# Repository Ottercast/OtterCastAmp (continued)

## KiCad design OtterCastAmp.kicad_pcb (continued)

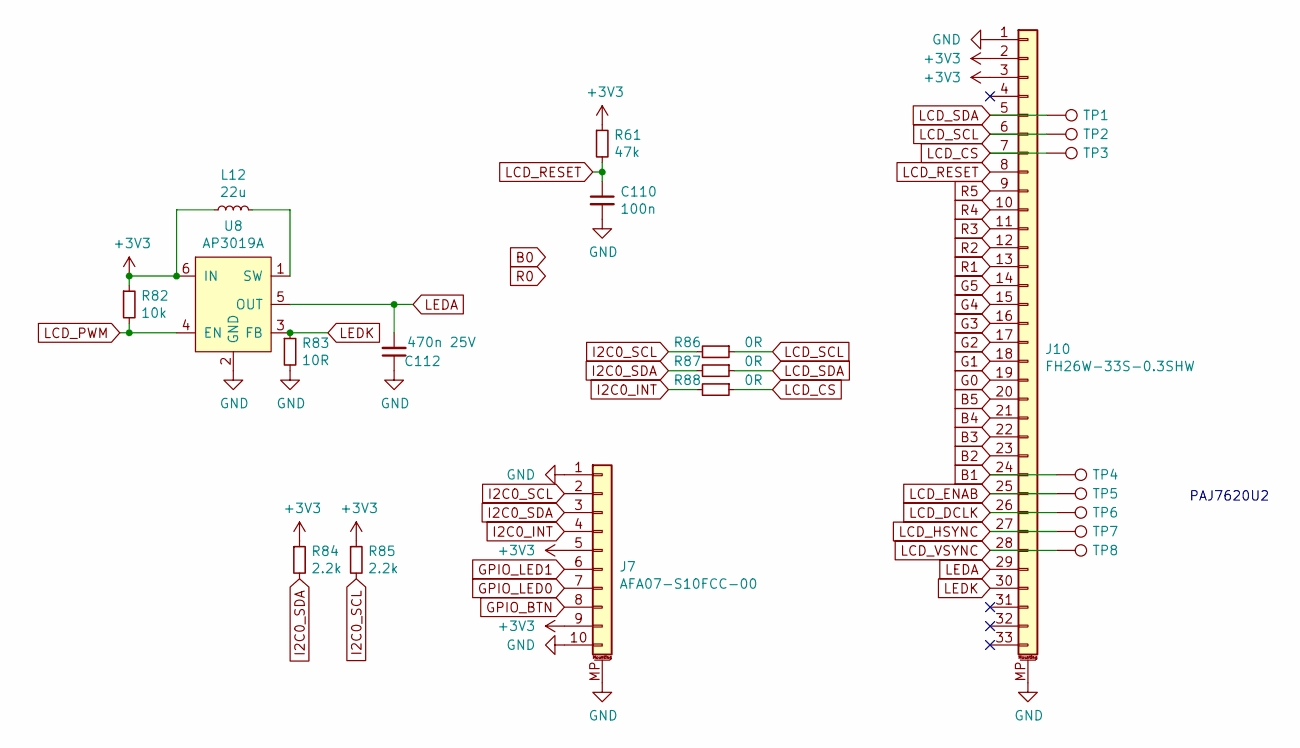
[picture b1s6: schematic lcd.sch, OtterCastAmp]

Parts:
C110: 100n; C_0402
C112: 470n 25V; C_0603
J7: AFA07-S10FCC-00; TE_1-84952-0_1x10-1MP_P1.0mm_Horizontal
J10: FH26W-33S-0.3SHW; Molex_502250-3391_2Rows-33Pins-1MP_P0.60mm_Horizontal
L12: 22u; Inductor_4040
R61: 47k; R_0402
R82: 10k; R_0402
R83: 10R; R_0402
R84, R85: 2.2k; R_0402
R86, R87, R88: 0R; R_0402
TP1, TP2, TP3, TP4, TP5, TP6, TP7, TP8: TestPoint; TestPoint_Pad_1.0x1.0mm
U8: AP3019A; SOT-23-6

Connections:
B1: J10.24, TP4.1; also elsewhere on the board
B2: J10.23; also elsewhere on the board
B3: J10.22; also elsewhere on the board
B4: J10.21; also elsewhere on the board
B5: J10.20; also elsewhere on the board
G0: J10.19; also elsewhere on the board
G1: J10.18; also elsewhere on the board
G2: J10.17; also elsewhere on the board
G3: J10.16; also elsewhere on the board
G4: J10.15; also elsewhere on the board
G5: J10.14; also elsewhere on the board
GND: C110.2, C112.1, J7.1, J7.10, J7.MP (MountPin), J10.1, J10.MP (MountPin), R83.2, U8.2 (GND); also elsewhere on the board
GPIO_BTN: J7.8; also elsewhere on the board
GPIO_LED0: J7.7; also elsewhere on the board
GPIO_LED1: J7.6; also elsewhere on the board
I2C0_INT: J7.4, R88.2; also elsewhere on the board
I2C0_SCL: J7.2, R85.2, R86.2; also elsewhere on the board
I2C0_SDA: J7.3, R84.2, R87.2; also elsewhere on the board
LCD_CS: J10.7, R88.1, TP3.1; also elsewhere on the board
LCD_DCLK: J10.26, TP6.1; also elsewhere on the board
LCD_ENAB: J10.25, TP5.1; also elsewhere on the board
LCD_HSYNC: J10.27, TP7.1; also elsewhere on the board
LCD_PWM: R82.2, U8.4 (EN); also elsewhere on the board
LCD_RESET: C110.1, J10.8, R61.2
LCD_SCL: J10.6, R86.1, TP2.1; also elsewhere on the board
LCD_SDA: J10.5, R87.1, TP1.1; also elsewhere on the board
LCD_VSYNC: J10.28, TP8.1; also elsewhere on the board
LEDA: C112.2, J10.29, U8.5 (OUT)
LEDK: J10.30, R83.1, U8.3 (FB)
unnamed: L12.2, U8.1 (SW)
R1: J10.13; also elsewhere on the board
R2: J10.12; also elsewhere on the board
R3: J10.11; also elsewhere on the board
R4: J10.10; also elsewhere on the board
R5: J10.9; also elsewhere on the board

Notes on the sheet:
PAJ7620U2

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
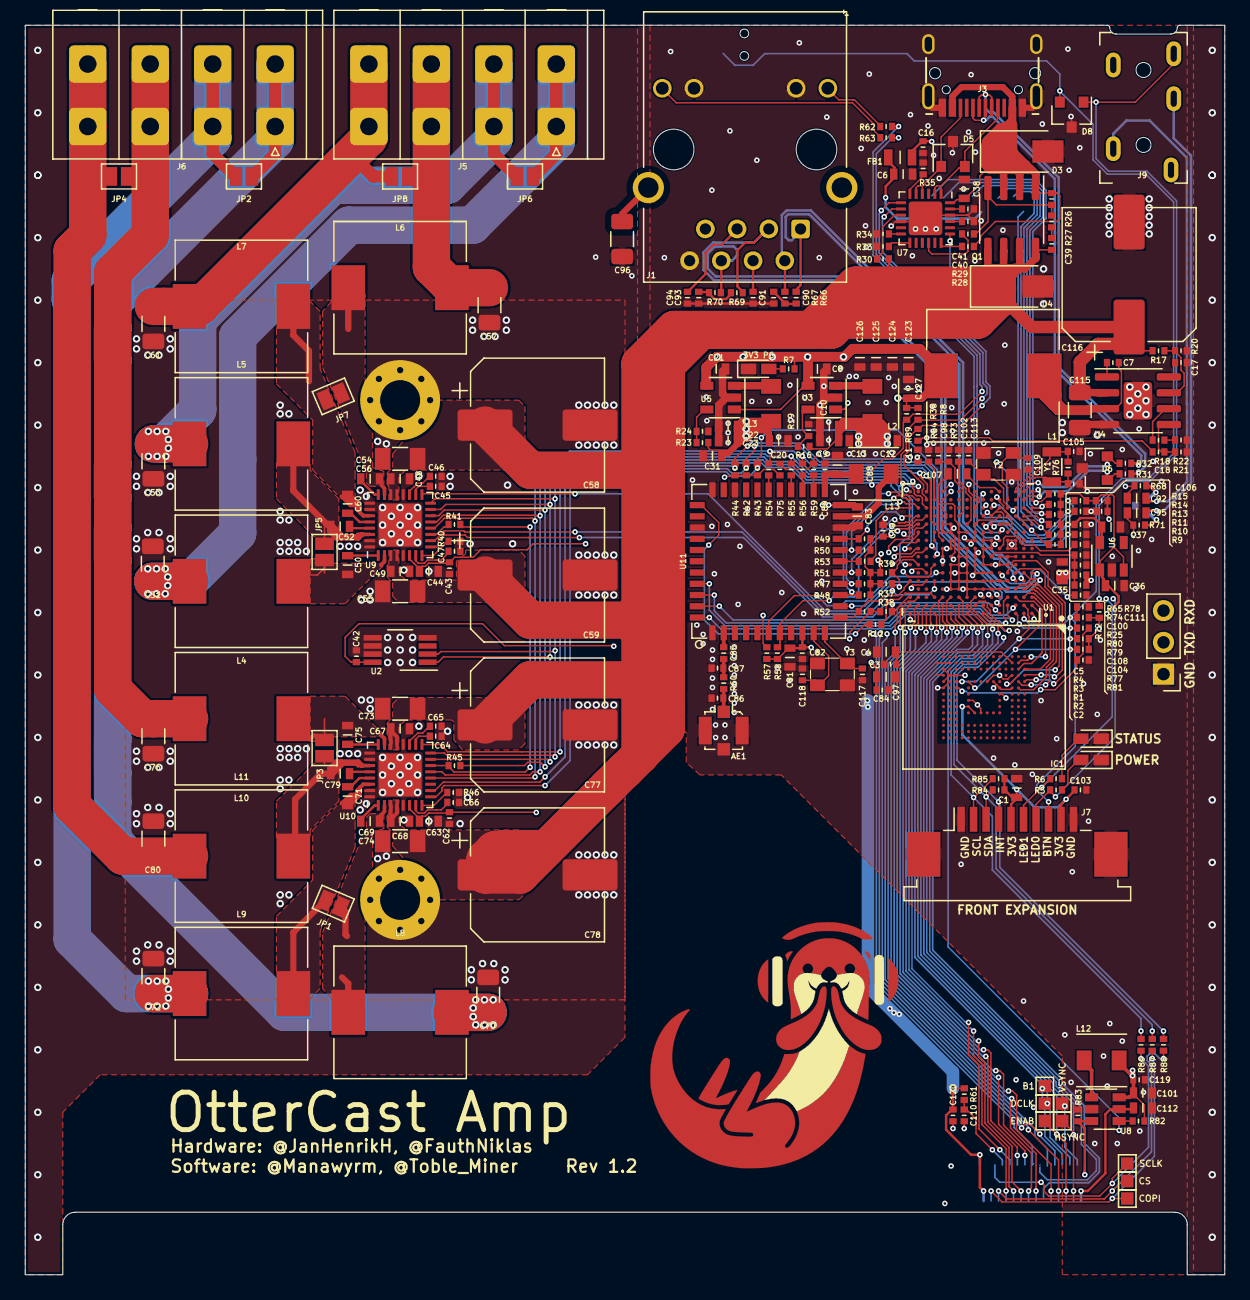
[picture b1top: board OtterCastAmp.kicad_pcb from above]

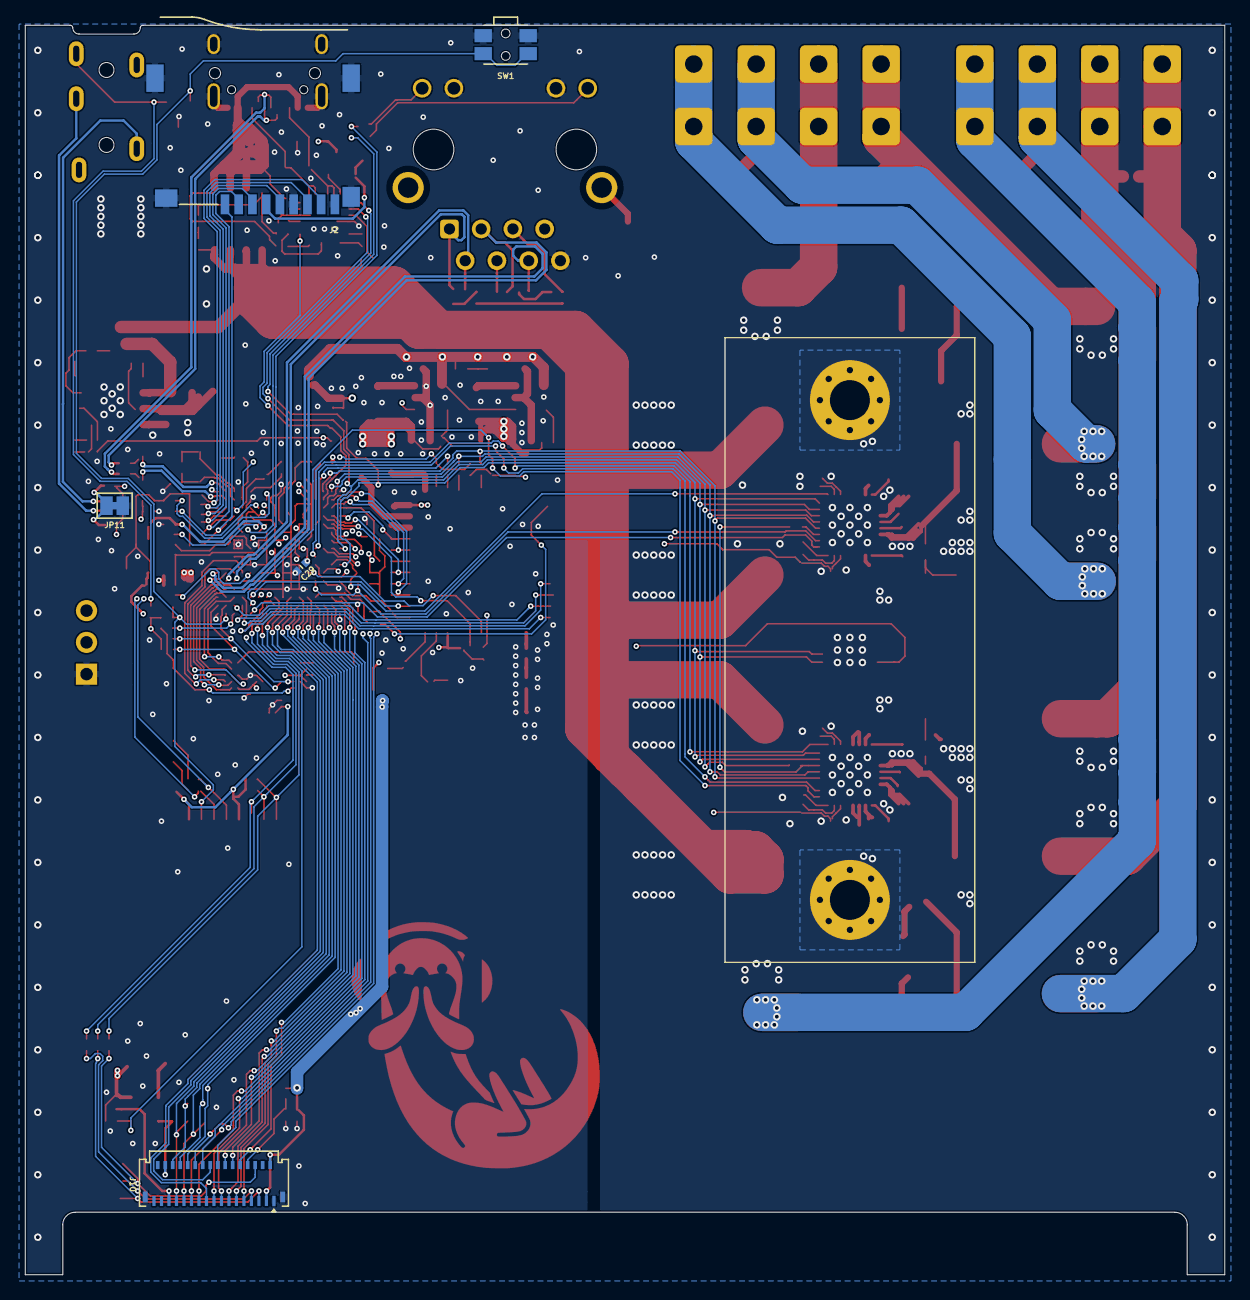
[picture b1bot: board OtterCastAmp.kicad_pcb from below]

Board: 4 copper layers, 96.0 x 100.0 mm, 269 parts (5 on the bottom side), 203 nets.

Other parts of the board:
3V3 PG: LED; LED_0603_1608Metric
B1: TestPoint; TestPoint_Pad_1.0x1.0mm
COPI: TestPoint; TestPoint_Pad_1.0x1.0mm
CS: TestPoint; TestPoint_Pad_1.0x1.0mm
DCLK: TestPoint; TestPoint_Pad_1.0x1.0mm
ENAB: TestPoint; TestPoint_Pad_1.0x1.0mm
HSYNC: TestPoint; TestPoint_Pad_1.0x1.0mm
SCLK: TestPoint; TestPoint_Pad_1.0x1.0mm
VSYNC: TestPoint; TestPoint_Pad_1.0x1.0mm

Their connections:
B1: B1.1; also elsewhere on the board
GND: 3V3 PG.1; also elsewhere on the board
LCD_CS: CS.1; also elsewhere on the board
LCD_DCLK: DCLK.1; also elsewhere on the board
LCD_ENAB: ENAB.1; also elsewhere on the board
LCD_HSYNC: HSYNC.1; also elsewhere on the board
LCD_SCL: SCLK.1; also elsewhere on the board
LCD_SDA: COPI.1; also elsewhere on the board
LCD_VSYNC: VSYNC.1; also elsewhere on the board
unnamed 141: 3V3 PG.2; also elsewhere on the board

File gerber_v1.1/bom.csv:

Comment,Designator,Footprint,LCSC Part #,LCSC Part Type
FH26W-33S-0.3SHW,J10,Molex_502250-3391_2Rows-33Pins-1MP_P0.60mm_Horizontal,,
EMMC04G-S100-B08U,IC1,MICRON_EMMC_153,C391255,
AllWinner-S3(FBGA-234),U1,FBGA-234(Pitch-0.65mm_Pad-0.3mm_11x11x1.08mm),,
GNDA,JP11,SolderJumper-2_P1.3mm_Bridged_Pad1.0x1.5mm,,
AP3019A,U8,SOT-23-6,C44956,
CONFIG,SW1,SW_SPST_EVQP7C,,
2.2k,"R85,R84,R36,R8,R7,R63,R62,R28,R79,R77,R6,R5",R_0402,C25879,
10R,R83,R_0402,C25077,
10k,"R82,R44,R43,R42,R39,R38,R37,R65",R_0402,C25744,
47k,"R61,R20,R18,R4,R2,R1,R58,R57,R52,R51,R50,R49,R48,R47,R15,R14,R13,R11,R10,R9",R_0402,C25792,
22u,L12,Inductor_4040,C135264,
JMP,"JP10,JP9",SolderJumper-2_P1.3mm_Bridged_Pad1.0x1.5mm,,
AFA07-S10FCC-00,J7,TE_1-84952-0_1x10-1MP_P1.0mm_Horizontal,,
ESD5302F,"D8,D6,D5",SOT-23,C313022,
470n 25V,"C112,C79,C75,C71,C69,C60,C56,C52,C50",C_0603,C170149,
100n,"C110,C120,C119,C42,C62,C43,C39,C11,C5,C3,C111,C108,C104,C103,C102,C100,C98,C94,C93,C91,C90,C89,C84,C82,C29,C19,C17,C16",C_0402,C1525,
0R,"R60,R41,R40,R32,R31",R_0402,C17168,
HR911105A,J1,RJ45_Hanrun_HR911105A,,
Micro_SD_Card,J2,SUNTECH_ST-TF-003A,,
LED,"D7,D2,D1",LED_0603,C2286,
10u,"C127,C126,C125,C124,C123,C63,C44,C37,C36,C23,C22,C21,C13,C12,C10,C9,C8,C4,C107,C101,C97,C88,C83,C81,C35,C31,C20,C6,C1",C_0603,C19702,
PBTL,"JP8,JP7,JP6,JP5,JP4,JP3,JP2,JP1",SolderJumper-2_P1.3mm_Open_Pad1.0x1.5mm,,
26MHz,Y3,Oscillator_3225,C70586,
18p,"C118,C117,C113,C109,C106,C105,C85",C_0402,C1549,
TAS5825MRHB,"U10,U9",Texas_S-PVQFN-N32_EP3.45x3.45mm,,
10u,"L11,L10,L9,L8,L7,L6,L5,L4",L_10.4x10.4_H4.8,C182194,
15uH,L1,L_10.4x10.4_H4.8,C182194,
STUSB4500,U7,QFN-24-1EP_4x4mm_P0.5mm_EP2.7x2.7mm,C506650,
470u 35V,"C116,C78,C77,C59,C58",CP_Elec_10x10.5,C3350,
22u 50V,"C115,C74,C73,C55,C54",C_1206_3216Metric,C12891,
100n 50V,"C68,C67,C49,C48",C_0603,C14663,
 C475204,"J6,J5",C475204,,
MP2303,U4,SOIC-8-1EP_3.9x4.9mm_P1.27mm_EP2.29x3mm,C18876,
LM75B,U2,VSSOP-8_3.0x3.0mm_P0.65mm,C33099,
100k,"R78,R35,R34,R33,R26,R24,R23,R17,R16",R_0402,C25741,
1k,"R46,R30",R_0402,C11702,
DNP,"R45,R71,R68",R_0402,,
22k,R29,R_0402,C25768,
100R,"R27,R56,R55,R54",R_0402,C25076,
5.6k,"R22,R75",R_0402,C25908,
15k,R21,R_0402,C25756,
68k,R19,R_0402,C36871,
22,"R3,R64,R59,R53,R25,R12",R_0402,C25092,
2.2uH,L13,Inductor_4040,C408335,
2u2,"L3,L2",Inductor_4040,C408335,
UART1,J4,PinHeader_1x03_P2.54mm_Vertical,,
3.2mm,"H2,H1",MountingHole_3.2mm_M3_Pad_Via,,
SMAJ22A ,"D4,D3",D_SMA,C148220,
1n 2kV,C96,C_1206_3216Metric,C35216,
1u 25V,"C95,C92,C38",C_0603,C15849,
680n 50V,"C80,C76,C72,C70,C61,C57,C53,C51",C_1206_3216Metric,C307578,
1u,"C66,C65,C64,C47,C46,C45,C41,C40",C_0402, C52923,
10n,C7,C_0402,C15195,
DNP,"C2,C87,C86",C_0402,,
u.FL,AE1,U.FL_Molex_MCRF_73412-0110_Vertical,,
24MHz,Y2,Oscillator_3225,C164058,
32.768kHz,Y1,Crystal_SMD_3215-2Pin_3.2x1.5mm,C32346,
AP6236,U11,LGA_44_12x12mm_0.9mm,,
MIC5501-3.0YM5,U6,SOT-23-5,C57079,
SY8089AAAC,"U5,U3",SOT-23-5,C78988,
240,"R81,R80",R_0402,C25094,
10M,R76,R_0402,C26082,
6k04,R74,R_0402,C25913,
200k,"R73,R72",R_0402,C25764,
51,"R70,R69,R67,R66",R_0402,C25125,
IRF8736,Q1,SOIC-8_150mil,C51630,
PJ-3270,J9,PJ-3270,,
USB,J3,USB-C 16Pin,C165948,
FERRET,FB1,R_0805,C1017,
3.3n,C18,C_0402,C26404,

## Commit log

2021-02-27 OtterCastAmp inital commit
2021-03-01 started layout
2021-03-01 layout final?
2021-03-03 V1.0 order release
2021-03-03 cleaned up libs
2021-03-03 cleaned up project
2021-04-12 V1.2 production release
2021-04-12 add jlc settings
2021-04-19 removed step files
2021-04-19 updated gitignore
2021-04-19 added license
2021-04-19 Create LICENSE
2021-04-19 fixed typo
2021-04-19 added Installation, fixed typo
2021-04-19 readd 3D files
2021-04-19 added licensing information to readme
2021-05-12 updated images
2021-05-12 removed note
2021-06-25 Add kitspace.yaml
2024-06-17 README: update webinterface screenshot to latest version
